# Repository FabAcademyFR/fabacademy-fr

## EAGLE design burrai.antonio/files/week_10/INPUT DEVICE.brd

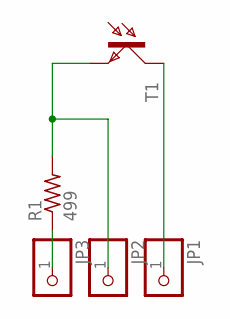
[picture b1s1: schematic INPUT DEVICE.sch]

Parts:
JP1, JP2, JP3: PINHD-1X1; 1X01
R1: 499; 1206
T1: PHOTOTRANSISTOR5MM; 5MM

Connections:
+5V: JP1.1, T1.IN (C)
unnamed: JP3.1, R1.1
unnamed: JP2.1, R1.2, T1.OUT (E)

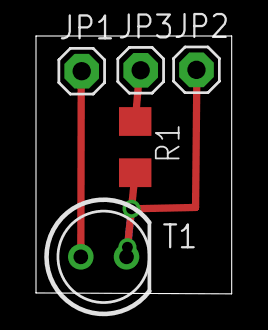
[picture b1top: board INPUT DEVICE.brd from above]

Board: 2 copper layers, 10.9 x 14.3 mm, 5 parts (0 on the bottom side), 3 nets.

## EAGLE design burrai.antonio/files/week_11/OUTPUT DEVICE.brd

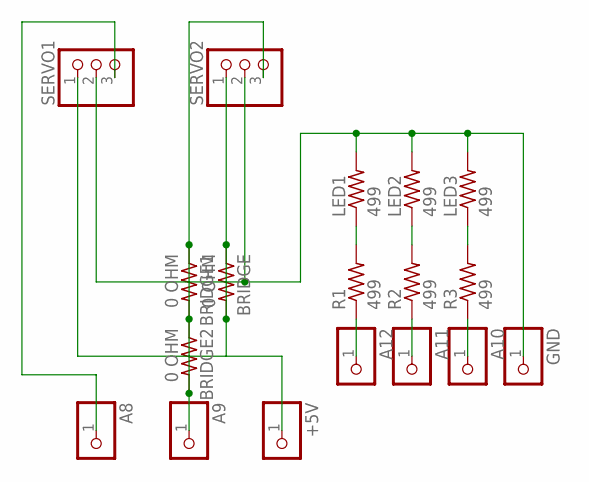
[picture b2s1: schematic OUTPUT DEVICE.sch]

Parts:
+5V: PINHD-1X1; 1X01
A8, A9, A10, A11, A12: PINHD-1X1; 1X01
BRIDGE, BRIDGE1, BRIDGE2: 0 OHM; 1206
GND: PINHD-1X1; 1X01
LED1, LED2, LED3: 499; 1206
R1, R2, R3: 499; 1206
SERVO1, SERVO2: PINHD-1X3; 1X03

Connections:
unnamed: GND.1, LED1.2, LED2.2, LED3.2, SERVO1.2, SERVO2.2
unnamed: LED1.1, R1.2
unnamed: A12.1, R1.1
unnamed: LED3.1, R3.2
unnamed: LED2.1, R2.2
unnamed: A11.1, R2.1
unnamed: A10.1, R3.1
unnamed: +5V.1, BRIDGE.1, BRIDGE.2, SERVO1.1, SERVO2.1
unnamed: A9.1, BRIDGE1.1, BRIDGE1.2, BRIDGE2.1, BRIDGE2.2, SERVO2.3
unnamed: A8.1, SERVO1.3

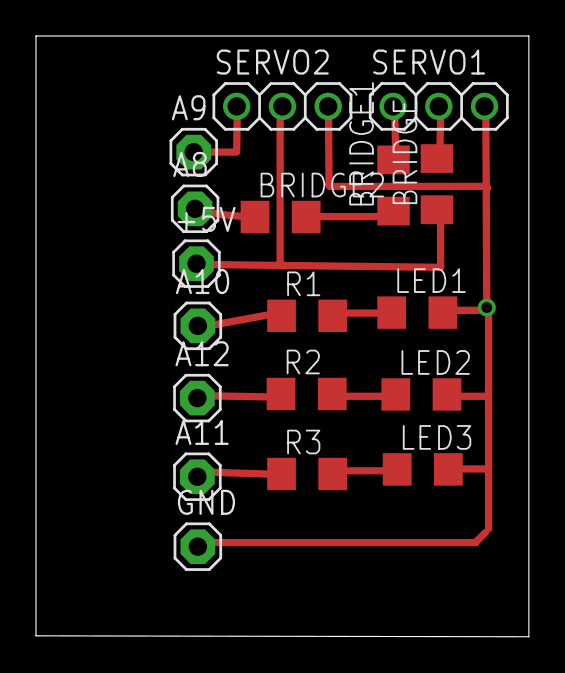
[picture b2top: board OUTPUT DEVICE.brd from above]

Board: 2 copper layers, 27.4 x 33.4 mm, 18 parts (0 on the bottom side), 10 nets.

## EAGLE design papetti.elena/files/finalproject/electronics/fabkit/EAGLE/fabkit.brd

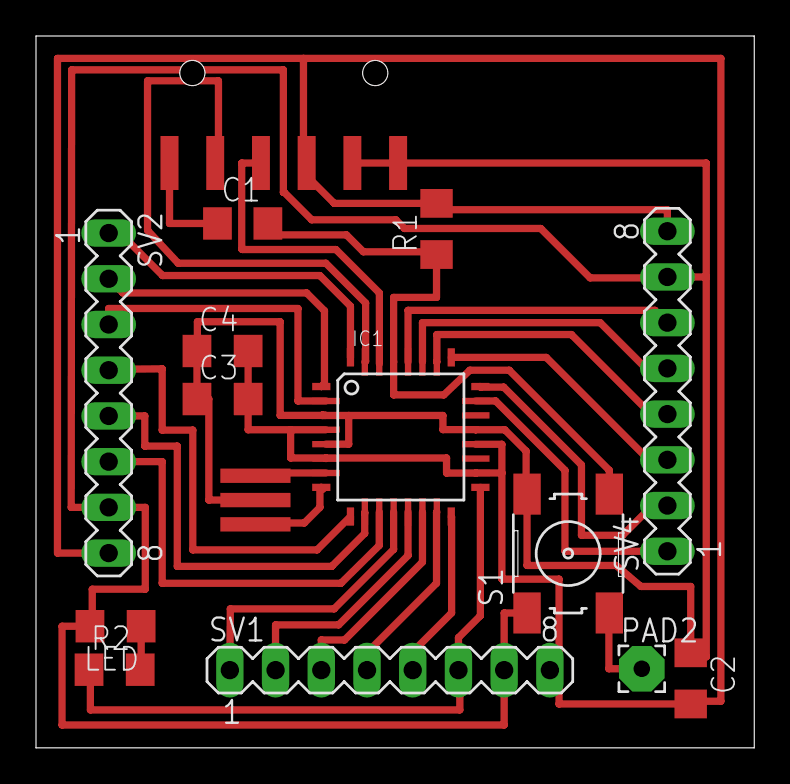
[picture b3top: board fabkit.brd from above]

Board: 2 copper layers, 39.9 x 39.5 mm, 15 parts (0 on the bottom side), 27 nets.

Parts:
C1: .1uf; C1206
C2: 1uf; 1206
C3: .1uf; 1206
C4: 10uf; 1206
IC1: ATMEGA48/88/168-AU; TQFP32-08
JP1: 1X06-SMD
LED: 1206
PAD2: WIREPAD2,54/0,9; 2,54/0,9
R1: 10k; 1206
R2: 499; 1206
S1: 6MM_SWITCH
SV1, SV2, SV4: MA08-1
U$2: RESONATOREFOB; EFOBM

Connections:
DTR: C1.1, JP1.6
GND: C2.1, C3.1, C4.1, IC1.3, IC1.5, IC1.21, JP1.1, JP1.2, LED.2, S1.1, S1.2, SV1.7, SV2.7, SV4.7, U$2.2
MISO: IC1.16, SV1.5
MOSI: IC1.15, SV1.4
unnamed: IC1.8, U$2.1
unnamed: IC1.12, SV1.1
unnamed: IC1.23, SV4.1
unnamed: IC1.24, SV4.2
unnamed: IC1.25, SV4.3
unnamed: IC1.26, SV4.4
unnamed: IC1.27, SV4.5
unnamed: IC1.28, SV4.6
unnamed: IC1.7, U$2.3
unnamed: IC1.32, SV2.1
unnamed: IC1.1, SV2.2
unnamed: IC1.2, SV2.3
unnamed: IC1.9, SV2.4
unnamed: IC1.10, SV2.5
unnamed: IC1.11, SV2.6
unnamed: IC1.13, SV1.2
unnamed: IC1.14, SV1.3
unnamed: LED.1, R2.2
RST: C1.2, IC1.29, PAD2.1, R1.1, S1.3, S1.4
RX: IC1.30, JP1.4
SCK: IC1.17, R2.1, SV1.6
TX: IC1.31, JP1.5
VCC: C2.2, C3.2, C4.2, IC1.4, IC1.6, IC1.18, IC1.20, JP1.3, R1.2, SV1.8, SV2.8, SV4.8

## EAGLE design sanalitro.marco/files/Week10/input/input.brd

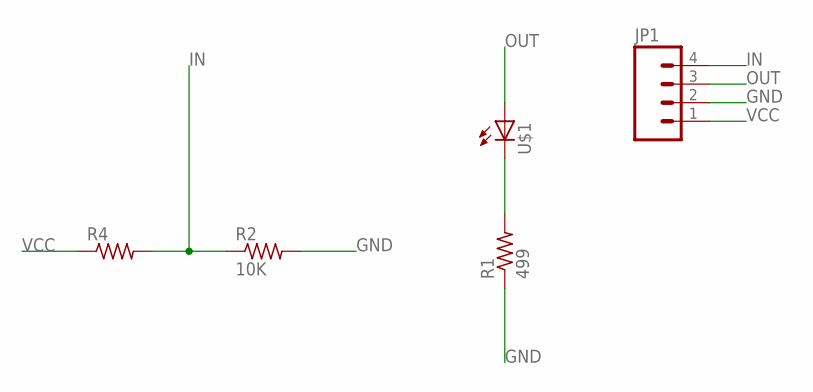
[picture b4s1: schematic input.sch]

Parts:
JP1: M04SMD; 1X04-SMD
R1: 499; 1206
R2: 10K; 1206
R4: R-US_V526-0; V526-0
U$1: LED1206; 1206

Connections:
GND: JP1.2, R1.1, R2.2
IN: JP1.4, R2.1, R4.2
unnamed: R1.2, U$1.2 (C)
OUT: JP1.3, U$1.1 (A)
VCC: JP1.1, R4.1

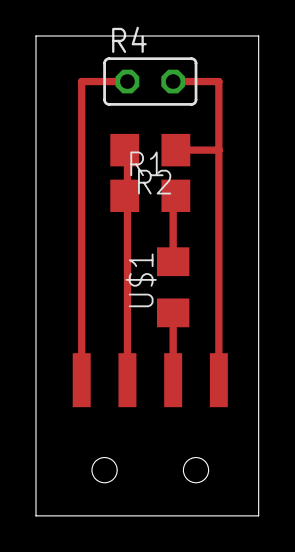
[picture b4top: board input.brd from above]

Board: 2 copper layers, 12.4 x 26.7 mm, 5 parts (0 on the bottom side), 5 nets.

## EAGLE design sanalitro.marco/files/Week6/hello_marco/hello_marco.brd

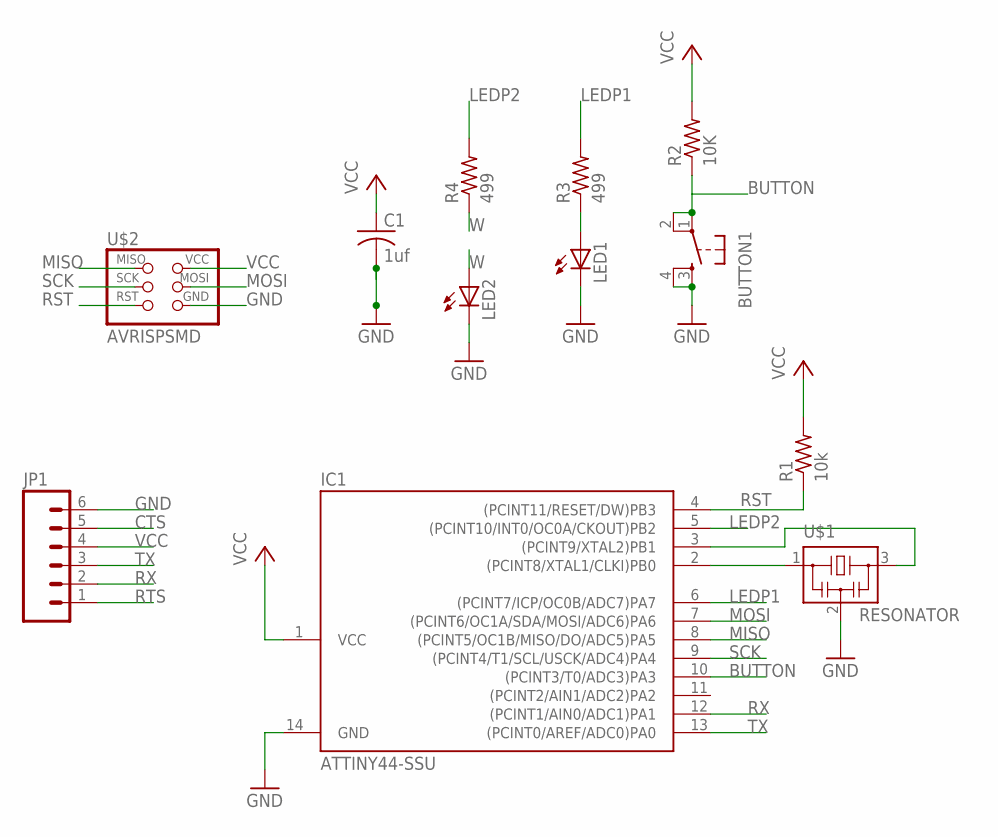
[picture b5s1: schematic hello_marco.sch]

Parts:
BUTTON1: 6MM_SWITCH6MM_SWITCH; 6MM_SWITCH
C1: 1uf; C1206
IC1: ATTINY44-SSU; SOIC14
JP1: M06SMD; 1X06-SMD
LED1, LED2: LED1206; 1206
R1: 10k; R1206
R2: 10K; 1206
R3, R4: 499; 1206
U$1: RESONATOR; EFOBM
U$2: AVRISPSMD; 2X03SMD

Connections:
BUTTON: IC1.10 ((PCINT3/T0/ADC3)PA3)
CTS: JP1.5
GND: BUTTON1.3 (S), BUTTON1.4 (S1), C1.2, IC1.14 (GND), JP1.6, LED1.2 (C), LED2.2 (C), U$1.2, U$2.6 (GND)
LEDP1: IC1.6 ((PCINT7/ICP/OC0B/ADC7)PA7), R3.2
LEDP2: IC1.5 ((PCINT10/INT0/OC0A/CKOUT)PB2), R4.2
MISO: IC1.8 ((PCINT5/OC1B/MISO/DO/ADC5)PA5), U$2.1 (MISO)
MOSI: IC1.7 ((PCINT6/OC1A/SDA/MOSI/ADC6)PA6), U$2.4 (MOSI)
unnamed: IC1.2 ((PCINT8/XTAL1/CLKI)PB0), U$1.1
unnamed: IC1.3 ((PCINT9/XTAL2)PB1), U$1.3
unnamed: LED1.1 (A), R3.1
unnamed: BUTTON1.1, BUTTON1.2 (P1), R2.1
RST: IC1.4 ((PCINT11/RESET/DW)PB3), R1.1, U$2.5 (RST)
RTS: JP1.1
RX: IC1.12 ((PCINT1/AIN0/ADC1)PA1), JP1.2
SCK: IC1.9 ((PCINT4/T1/SCL/USCK/ADC4)PA4), U$2.3 (SCK)
TX: IC1.13 ((PCINT0/AREF/ADC0)PA0), JP1.3
VCC: C1.1, IC1.1 (VCC), JP1.4, R1.2, R2.2, U$2.2 (VCC)
W: LED2.1 (A), R4.1

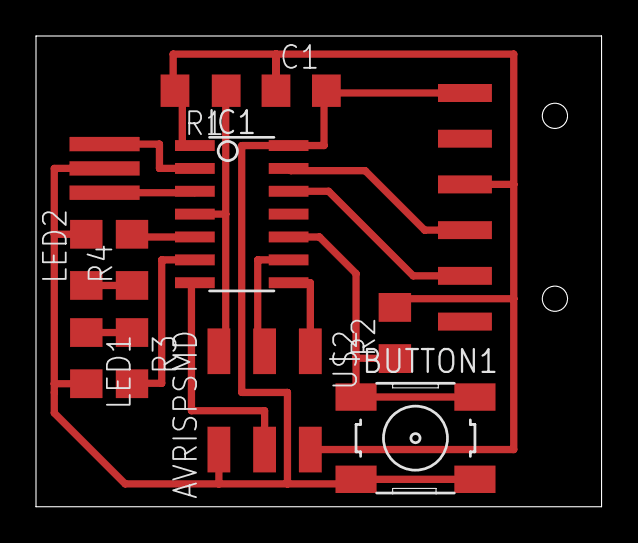
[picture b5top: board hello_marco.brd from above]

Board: 1 copper layer, 31.4 x 26.2 mm, 12 parts (0 on the bottom side), 15 nets.

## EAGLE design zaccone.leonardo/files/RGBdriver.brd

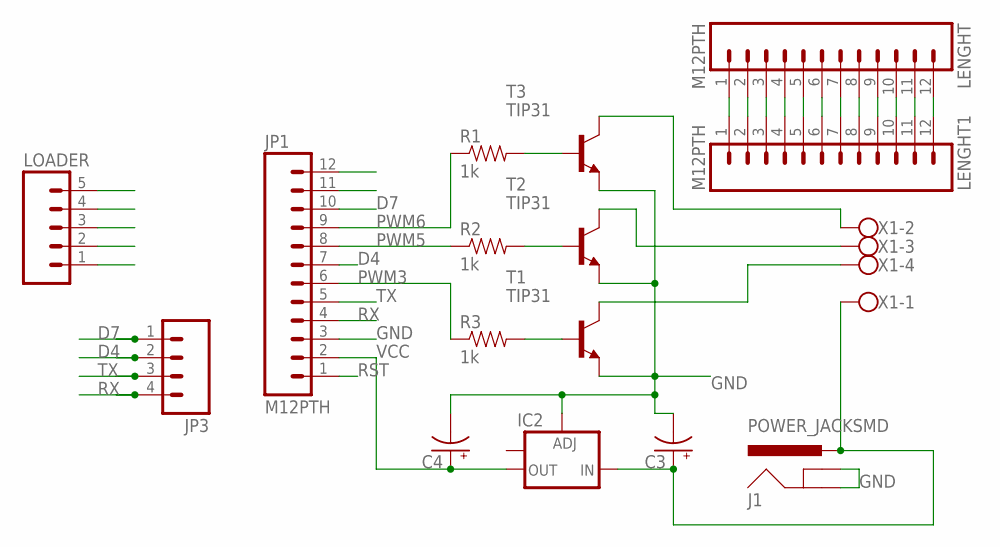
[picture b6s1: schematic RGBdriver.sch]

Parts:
C3, C4: CAP_POLC; PANASONIC_C
IC2: V_REG_LM1117SOT223; SOT223
J1: POWER_JACKSMD; POWER_JACK_SMD
JP1: M12PTH; 1X12
JP3: M04PTH; 1X04
LENGHT, LENGHT1: M12PTH; 1X12
LOADER: M05PTH; 1X05
R1, R2, R3: 1k; 1206
T1, T2, T3: TIP31; TO220
X1: W237-4

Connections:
D4: JP1.7, JP3.2
D7: JP1.10, JP3.1
GND: C3.-, C4.-, IC2.1 (ADJ), J1.GND (GNDBREAK), J1.GNDBREAK (GND), JP1.3, JP1.11, JP1.12, LENGHT.6, LENGHT.12, LENGHT1.6, LENGHT1.12, LOADER.3, T1.3 (E), T2.3 (E), T3.3 (E)
unnamed: LENGHT.1, LENGHT1.1
unnamed: R1.2, T3.1 (B)
unnamed: R3.2, T1.1 (B)
unnamed: T3.2 (C), X1.2
unnamed: T2.2 (C), X1.3
unnamed: LENGHT.2, LENGHT1.2
unnamed: R2.2, T2.1 (B)
unnamed: T1.2 (C), X1.4
unnamed: C3.+, IC2.3 (IN), J1.VIN0 (PWR), X1.1
unnamed: LENGHT.3, LENGHT1.3
unnamed: LENGHT.4, LENGHT1.4
unnamed: LENGHT.5, LENGHT1.5
unnamed: LENGHT.7, LENGHT1.7
unnamed: LENGHT.8, LENGHT1.8
unnamed: LENGHT.9, LENGHT1.9
unnamed: LENGHT.10, LENGHT1.10
unnamed: LENGHT.11, LENGHT1.11
PWM3: JP1.6, R3.1
PWM5: JP1.8, R2.1
PWM6: JP1.9, R1.1
RST: JP1.1, LOADER.1
RX: JP1.4, JP3.4, LOADER.4
TX: JP1.5, JP3.3, LOADER.5
VCC: C4.+, IC2.2 (OUT), JP1.2, LOADER.2

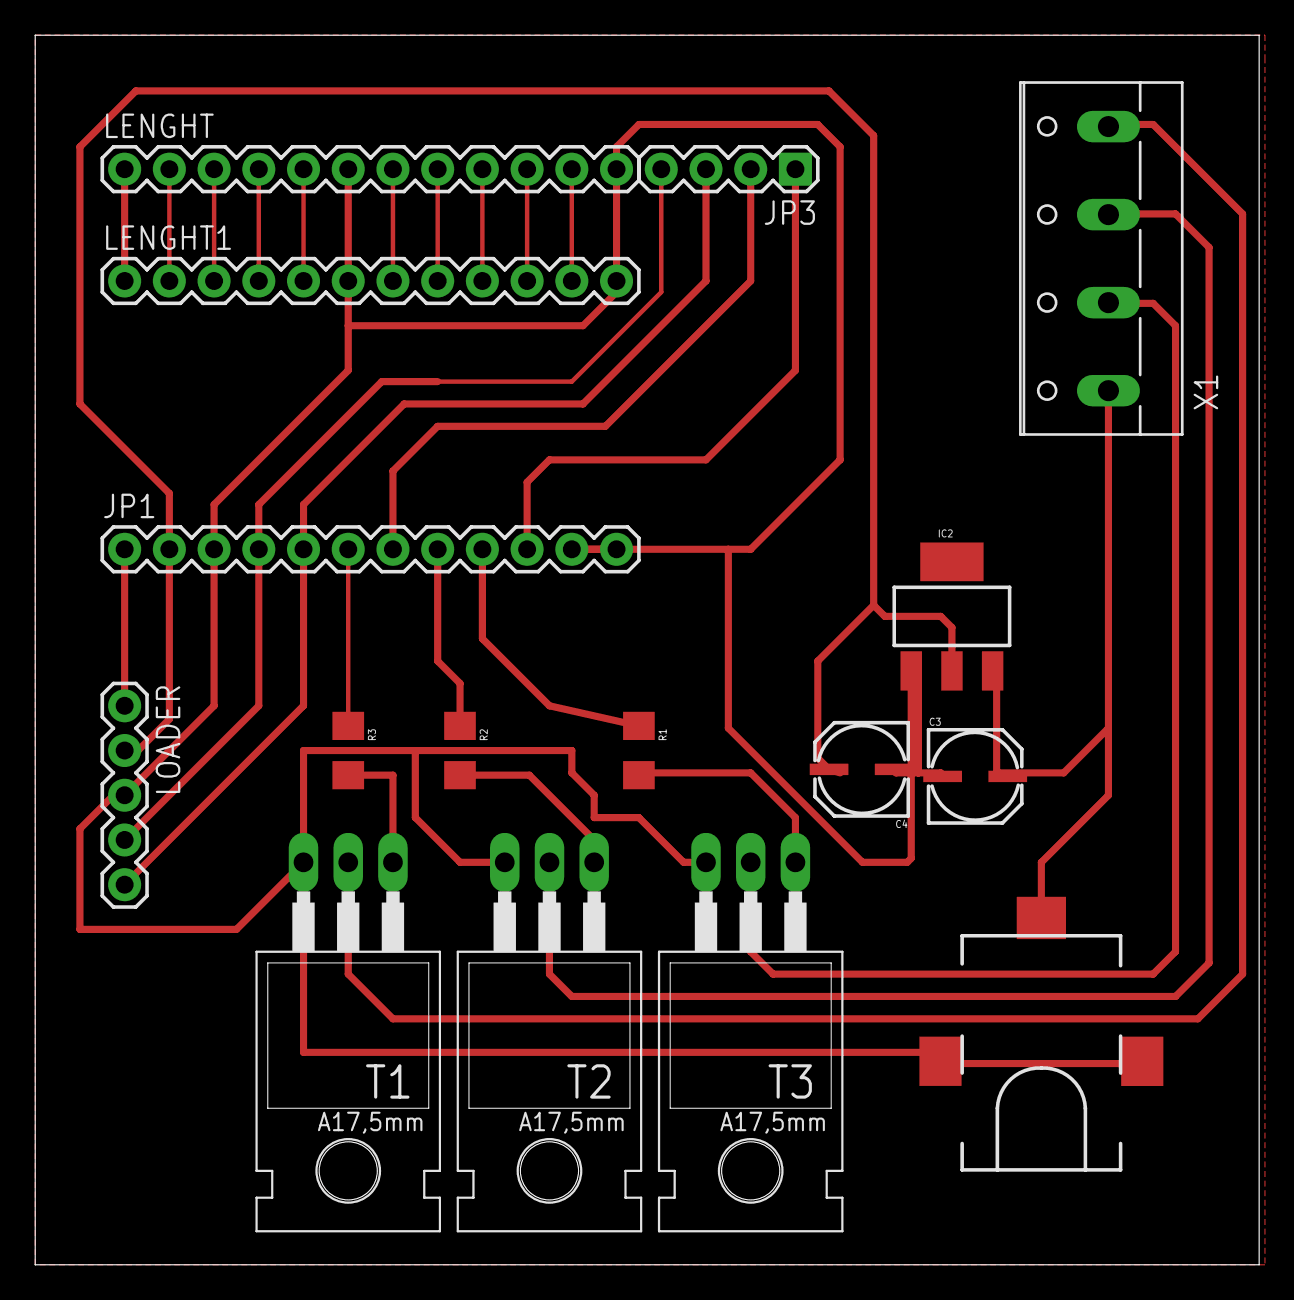
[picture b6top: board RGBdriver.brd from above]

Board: 2 copper layers, 69.5 x 69.8 mm, 16 parts (0 on the bottom side), 27 nets.

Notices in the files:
parts and their libraries:
01_SparkFun: Licensing: CC v3.0 Share-Alike You are welcome to use this library for commercial purposes.
